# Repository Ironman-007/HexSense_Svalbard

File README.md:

# HexSense_Svalbard

The HexSense sensor node design for Svalbard mission in July, 2023

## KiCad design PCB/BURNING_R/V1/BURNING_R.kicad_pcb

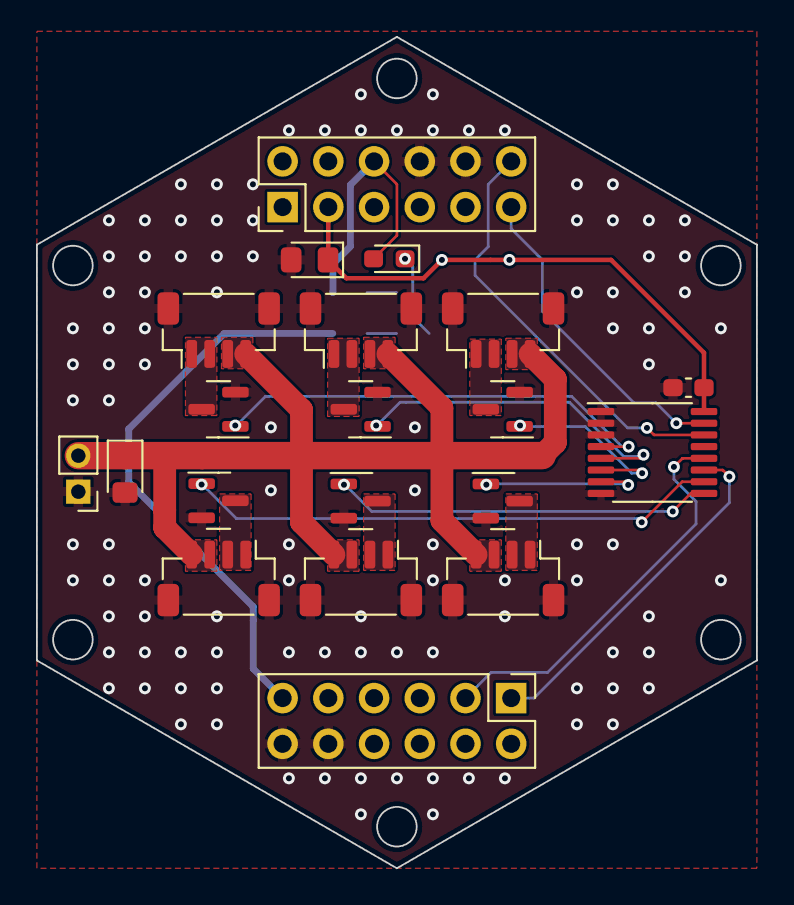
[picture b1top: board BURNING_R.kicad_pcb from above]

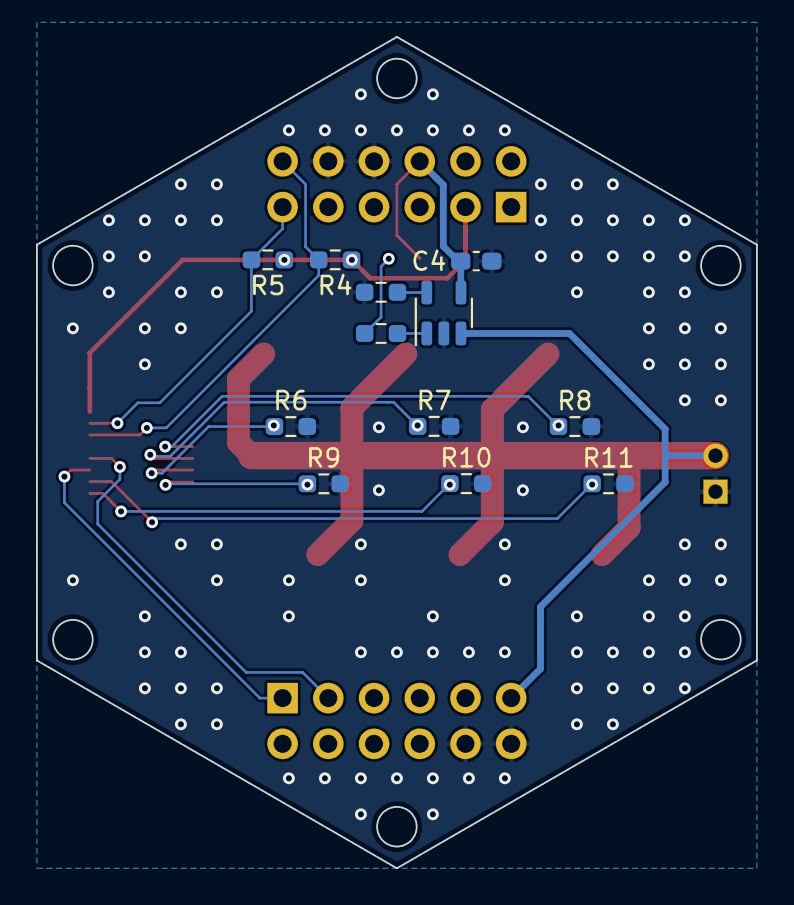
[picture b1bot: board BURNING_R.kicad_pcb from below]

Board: 2 copper layers, 40.0 x 46.2 mm, 32 parts (12 on the bottom side), 23 nets.

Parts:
C1, C3: 47uF; LED_0805_2012Metric_Pad1.15x1.40mm_HandSolder
C2, C4: 0.1uF; C_0603_1608Metric_Pad1.08x0.95mm_HandSolder
D1: RED; LED_0603_1608Metric_Pad1.05x0.95mm_HandSolder
J1, J2: Conn_02x06_Odd_Even; PinHeader_2x06_P2.54mm_Vertical
J3, J4, J5, J6, J7, J8: BR_conn; JST_SH_BM04B-SRSS-TB_1x04-1MP_P1.00mm_Vertical
J9: Battery; PinHeader_1x02_P2.00mm_Vertical
Q1, Q2, Q3, Q4, Q5, Q6: DMN2056U; SOT-23
R1, R2: 1k; R_0603_1608Metric_Pad0.98x0.95mm_HandSolder
R4, R5: NC; R_0603_1608Metric_Pad0.98x0.95mm_HandSolder
R6, R7, R8, R9, R10, R11: 10k; R_0603_1608Metric_Pad0.98x0.95mm_HandSolder
U1: TCA9534; TSSOP-16_4.4x5mm_P0.65mm
U2: MCP73831-2-OT; SOT-23-5

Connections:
+5V: C4.1, D1.2 (A), J1.6, U2.4 (VDD)
/BAT_BR: C3.1, J2.11, J3.3, J3.4, J4.3, J4.4, J5.3, J5.4, J6.3, J6.4, J7.3, J7.4, J8.3, J8.4, J9.2, U2.3 (VBAT)
/BR_1: J3.1, J3.2, Q1.3 (D)
/BR_1_EN: Q1.1 (G), R11.1, U1.10 (P5)
/BR_2: J4.1, J4.2, Q2.3 (D)
/BR_2_EN: Q2.1 (G), R10.1, U1.9 (P4)
/BR_3: J5.1, J5.2, Q3.3 (D)
/BR_3_EN: Q3.1 (G), R9.1, U1.7 (P3)
/BR_4: J6.1, J6.2, Q4.3 (D)
/BR_4_EN: Q4.1 (G), R8.1, U1.4 (P0)
/BR_5: J7.1, J7.2, Q5.3 (D)
/BR_5_EN: Q5.1 (G), R7.1, U1.5 (P1)
/BR_6: J8.1, J8.2, Q6.3 (D)
/BR_6_EN: Q6.1 (G), R6.1, U1.6 (P2)
/P1: J2.1, U1.11 (P6)
/P2: J2.3, U1.12 (P7)
/SCL: J1.12, R4.2, U1.14 (SCL)
/SDA: J1.11, R5.2, U1.15 (SDA)
GND: C1.2, C2.2, C3.2, C4.2, J1.8, J1.10, J2.10, J2.12, J3.MP, J4.MP, J5.MP, J6.MP, J7.MP, J8.MP, J9.1, Q1.2 (S), Q2.2 (S), Q3.2 (S), Q4.2 (S), Q5.2 (S), Q6.2 (S), R1.1, R6.2, R7.2, R8.2, R9.2, R10.2, R11.2, U1.1 (A0), U1.2 (A1), U1.3 (A2), U1.8 (GND), U2.2 (VSS)
unnamed: D1.1 (K), R2.2
unnamed: R1.2, U2.5 (PROG)
unnamed: R2.1, U2.1 (STAT)
VCC: C1.1, C2.1, J1.3, R4.1, R5.1, U1.16 (VDD)

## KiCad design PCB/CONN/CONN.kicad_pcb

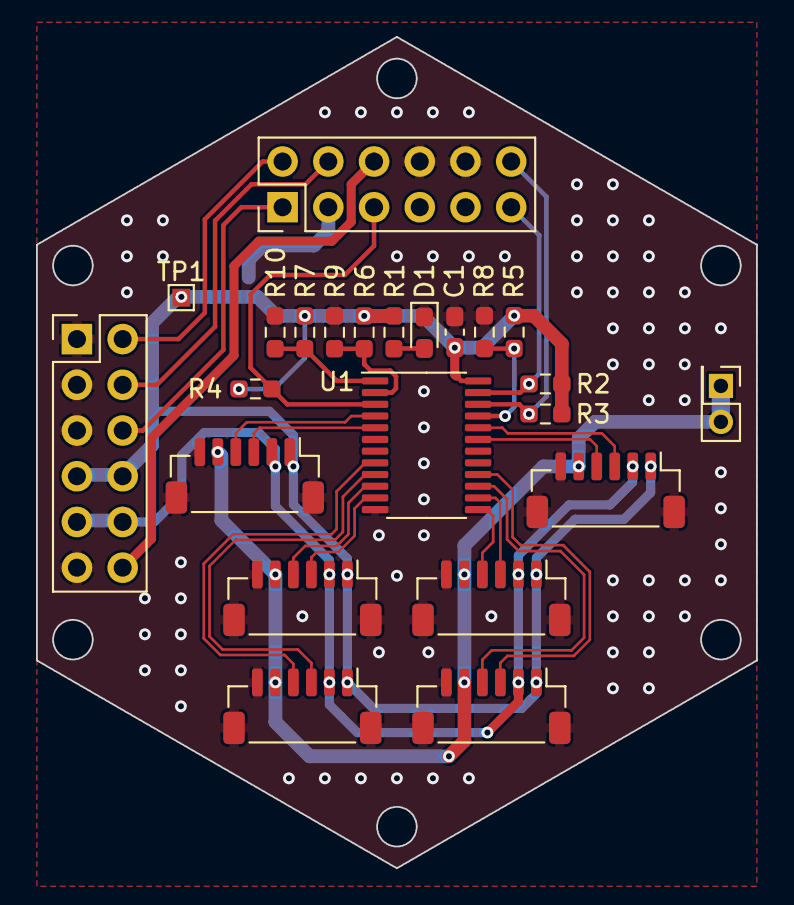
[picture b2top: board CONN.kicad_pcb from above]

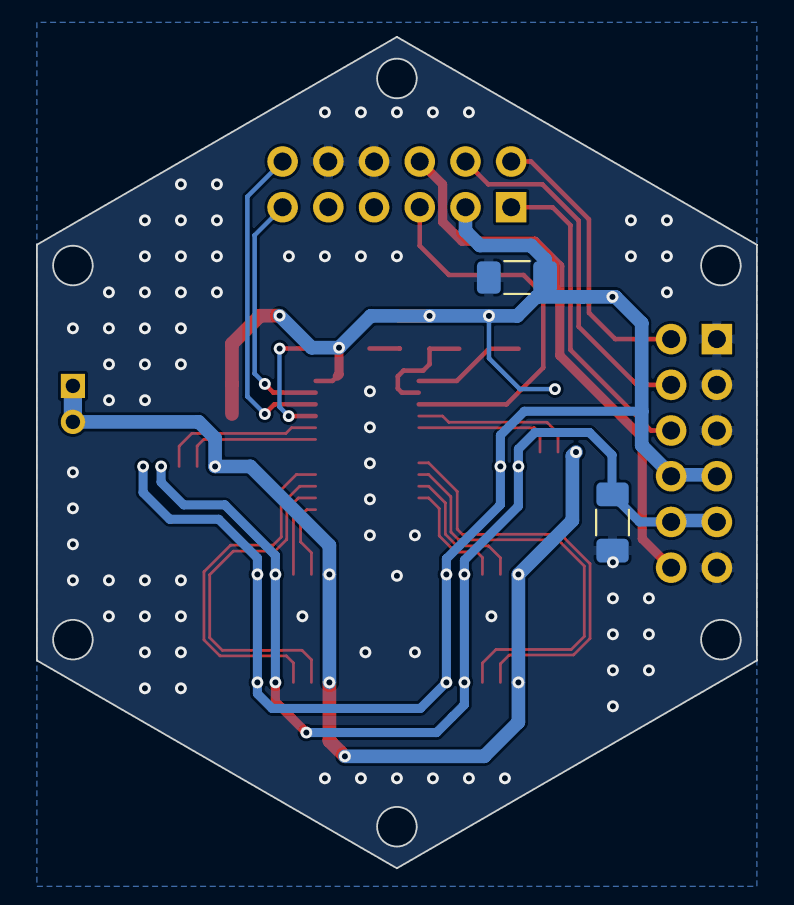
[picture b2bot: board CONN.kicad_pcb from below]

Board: 2 copper layers, 40.0 x 46.2 mm, 25 parts (2 on the bottom side), 27 nets.

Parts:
C1: 0.1uF; C_0603_1608Metric_Pad1.08x0.95mm_HandSolder
C2, C3: 47uF; C_1206_3216Metric_Pad1.33x1.80mm_HandSolder
D1: RED; LED_0603_1608Metric_Pad1.05x0.95mm_HandSolder
J1, J3: Conn_02x06_Odd_Even; PinHeader_2x06_P2.54mm_Vertical
J2: Solar cell; PinHeader_2x01_P2.00mm_Vertical
J4, J5, J6, J7, J8, J9: BM06B-SURS-TF(LF)(SN); JST_SH_BM06B-SRSS-TB_1x06-1MP_P1.00mm_Vertical
R1, R2, R3: 4.7K; R_0603_1608Metric_Pad0.98x0.95mm_HandSolder
R4, R8, R9, R10: 10k; R_0603_1608Metric_Pad0.98x0.95mm_HandSolder
R5, R6, R7: NC; R_0603_1608Metric_Pad0.98x0.95mm_HandSolder
TP1: TestPoint_Alt; TestPoint_Pad_1.0x1.0mm
U1: TCA9548APWR; TSSOP-24_4.4x7.8mm_P0.65mm

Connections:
+1V8: C3.1, J1.9, J1.10, J4.2, J5.2, J6.2, J7.2, J8.2, J9.2
+3V3: C1.1, C2.1, J1.7, J1.8, J3.3, J4.1, J5.1, J6.1, J7.1, J8.1, J9.1, R1.2, R2.2, R3.2, R4.2, R5.2, R6.2, R7.2, TP1.1, U1.24 (VCC)
+5V: J1.12, J3.6
/SC: J2.1, J2.2, J4.5, J5.5, J6.5, J7.5, J8.5, J9.5
/SCL: J3.12, R3.1, U1.22 (SCL)
/SCL0: J6.3, U1.5 (SC0)
/SCL2: J4.3, U1.9 (SC2)
/SCL3: J7.3, U1.11 (SC3)
/SCL4: J5.3, U1.14 (SC4)
/SCL5: J9.3, U1.16 (SC5)
/SCL7: J8.3, U1.20 (SC7)
/SDA: J3.11, R2.1, U1.23 (SDA)
/SDA0: J6.4, U1.4 (SD0)
/SDA2: J4.4, U1.8 (SD2)
/SDA3: J7.4, U1.10 (SD3)
/SDA4: J5.4, U1.13 (SD4)
/SDA5: J9.4, U1.15 (SD5)
/SDA7: J8.4, U1.19 (SD7)
/VBAT: J1.6, J3.1
/VBAT_OK: J1.4, J3.4
/~EN: J1.2, J3.2
/~RESET: J3.5, R4.1, U1.3 (~RESET)
GND: C1.2, C2.2, C3.2, D1.1 (K), J1.1, J1.3, J1.5, J1.11, J3.8, J3.10, J4.6, J4.MP, J5.6, J5.MP, J6.6, J6.MP, J7.6, J7.MP, J8.6, J8.MP, J9.6, J9.MP, R8.1, R9.1, R10.1, U1.12 (GND)
unnamed: D1.2 (A), R1.1
unnamed: R5.1, R8.2, U1.21 (A2)
unnamed: R6.1, R9.2, U1.2 (A1)
unnamed: R7.1, R10.2, U1.1 (A0)

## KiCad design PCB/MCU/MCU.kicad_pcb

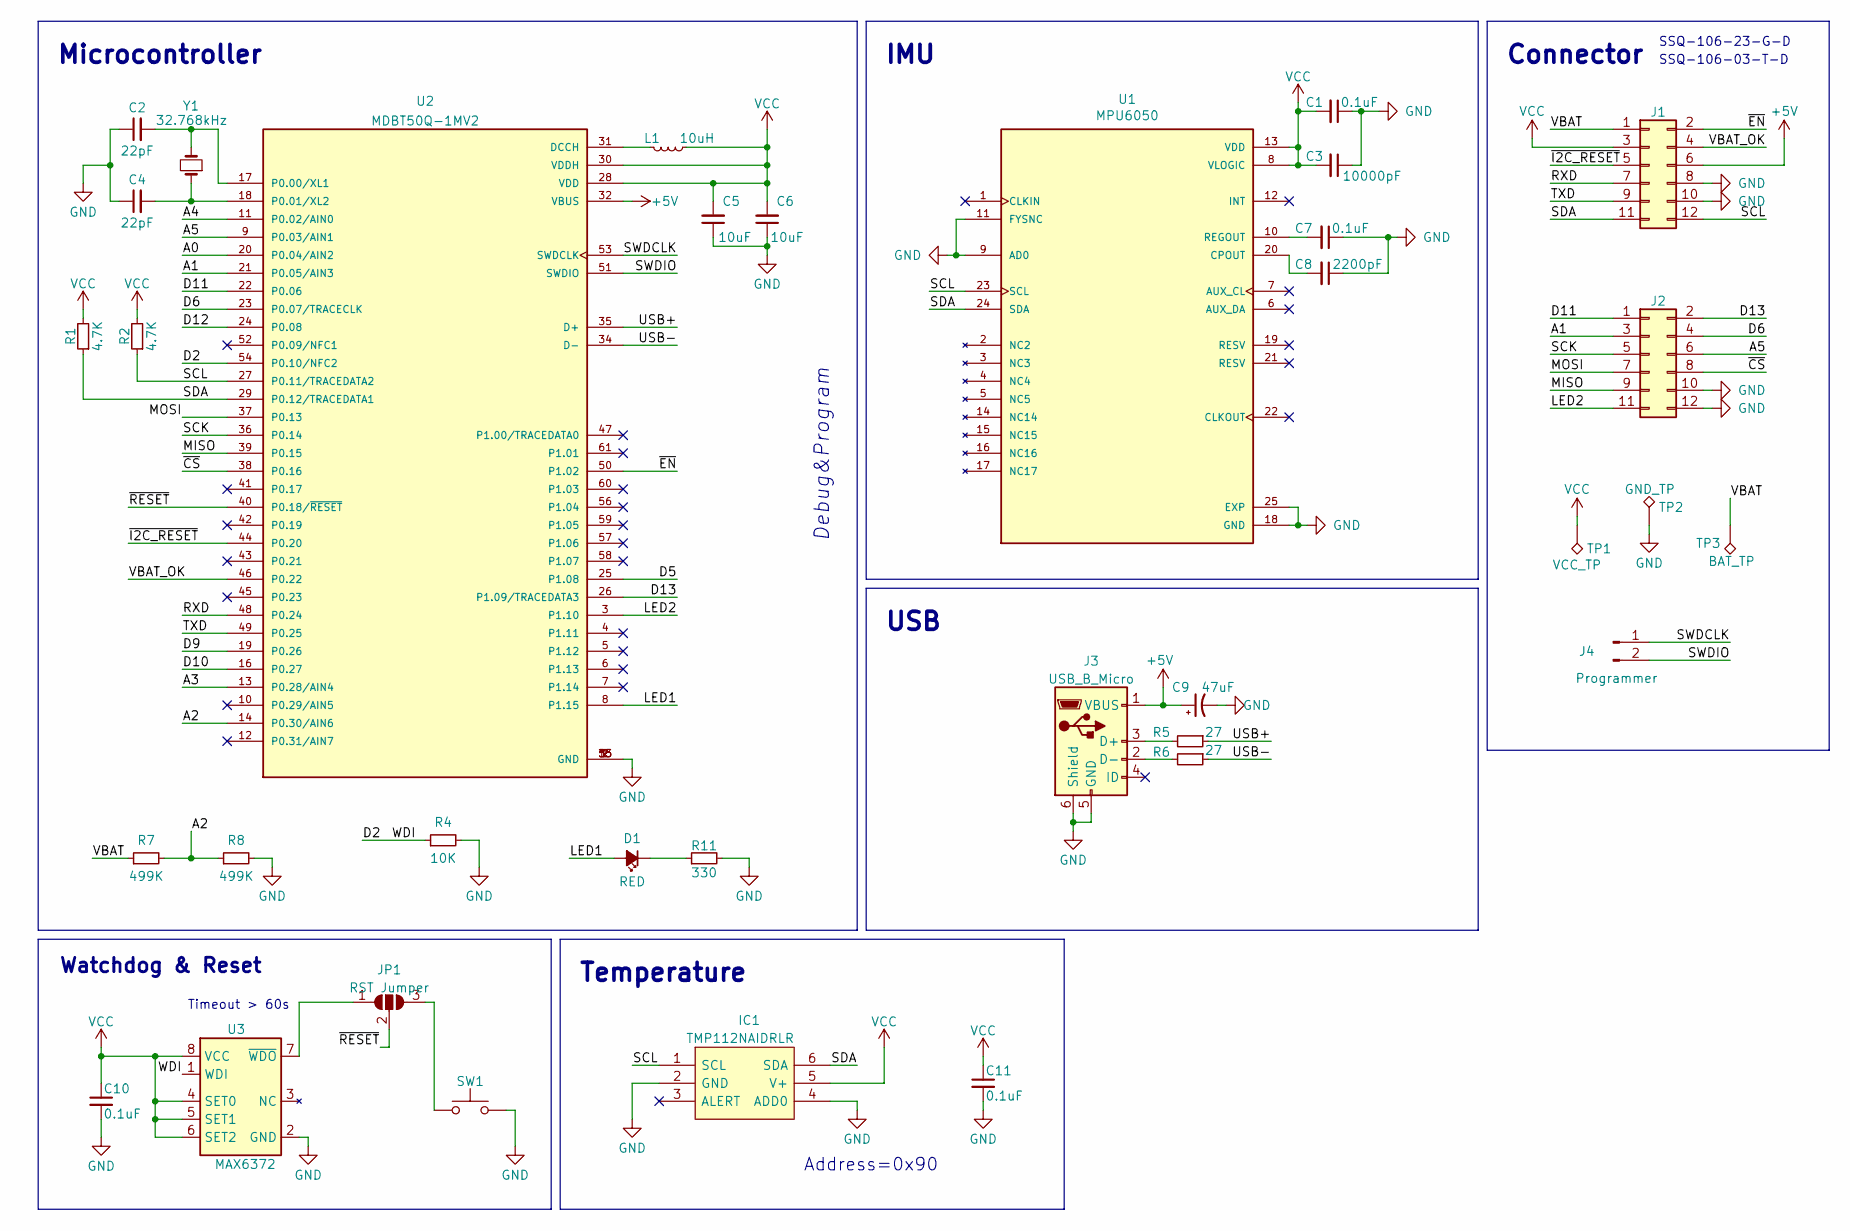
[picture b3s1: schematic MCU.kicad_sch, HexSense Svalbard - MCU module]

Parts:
C1, C7, C10, C11: 0.1uF; C_0402_1005Metric
C2, C4: 22pF; C_0402_1005Metric_Pad0.74x0.62mm_HandSolder
C3: 10000pF; C_0402_1005Metric
C5, C6: 10uF; C_0402_1005Metric_Pad0.74x0.62mm_HandSolder
C8: 2200pF; C_0402_1005Metric
C9: 47uF; C_0805_2012Metric_Pad1.18x1.45mm_HandSolder
D1: RED; LED_0603_1608Metric_Pad1.05x0.95mm_HandSolder
IC1: TMP112NAIDRLR; SOT50P160X60-6N; Manufacturer_Part_Number TMP112NAIDRLR; Mouser Part Number 595-TMP112NAIDRLR
J1, J2: Conn_02x06_Odd_Even; PinHeader_2x06_P2.54mm_Vertical
J3: USB_B_Micro; USB_Micro-B_Amphenol_10104110_Horizontal
J4: Programmer; PinHeader_1x02_P2.54mm_Vertical
JP1: RST Jumper; SolderJumper-3_P1.3mm_Open_RoundedPad1.0x1.5mm
L1: 10uH; L_0603_1608Metric_Pad1.05x0.95mm_HandSolder
R1, R2: 4.7K; R_0402_1005Metric_Pad0.72x0.64mm_HandSolder
R4: 10K; R_0402_1005Metric
R5, R6: 27; R_0402_1005Metric_Pad0.72x0.64mm_HandSolder
R7, R8: 499K; R_0402_1005Metric_Pad0.72x0.64mm_HandSolder
R11: 330; R_0402_1005Metric_Pad0.72x0.64mm_HandSolder
SW1: SW_Push; SW_Push_1P1T_NO_CK_KMR2
TP1: VCC_TP; TestPoint_Pad_1.5x1.5mm
TP2: GND_TP; TestPoint_Pad_1.5x1.5mm
TP3: BAT_TP; TestPoint_Pad_1.0x1.0mm
U1: MPU6050; IC_MPU6050; PARTREV 3.4
U2: MDBT50Q-1MV2; XCVR_MDBT50Q-1MV2; PARTREV H
U3: MAX6372; SOT-23-8
Y1: 32.768kHz; C_0805_2012Metric_Pad1.18x1.45mm_HandSolder

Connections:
+5V: C9.1, J1.6, J3.1 (VBUS), U2.32 (VBUS)
/A0: U2.20 (P0.04/AIN2)
/A1: J2.3, U2.21 (P0.05/AIN3)
/A2: R7.2, R8.1, U2.14 (P0.30/AIN6)
/A3: U2.13 (P0.28/AIN4)
/A4: U2.11 (P0.02/AIN0)
/A5: J2.6, U2.9 (P0.03/AIN1)
/D2: R4.1, U2.54 (P0.10/NFC2), U3.1 (WDI)
/D5: U2.25 (P1.08)
/D6: J2.4, U2.23 (P0.07/TRACECLK)
/D9: U2.19 (P0.26)
/D10: U2.16 (P0.27)
/D11: J2.1, U2.22 (P0.06)
/D12: U2.24 (P0.08)
/D13: J2.2, U2.26 (P1.09/TRACEDATA3)
/LED1: D1.2 (A), U2.8 (P1.15)
/LED2: J2.11, U2.3 (P1.10)
/MISO: J2.9, U2.39 (P0.15)
/MOSI: J2.7, U2.37 (P0.13)
/RXD: J1.7, U2.48 (P0.24)
/SCK: J2.5, U2.36 (P0.14)
/SCL: IC1.1 (SCL), J1.12, R2.1, U1.23 (SCL), U2.27 (P0.11/TRACEDATA2)
/SDA: IC1.6 (SDA), J1.11, R1.1, U1.24 (SDA), U2.29 (P0.12/TRACEDATA1)
/SWDCLK: J4.1, U2.53 (SWDCLK)
/SWDIO: J4.2, U2.51 (SWDIO)
/TXD: J1.9, U2.49 (P0.25)
/USB+: R5.1, U2.35 (D+)
/USB-: R6.1, U2.34 (D-)
/VBAT: J1.1, R7.1, TP3.1
/VBAT_OK: J1.4, U2.46 (P0.22)
/~CS: J2.8, U2.38 (P0.16)
/~EN: J1.2, U2.50 (P1.02)
/~I2C_RESET: J1.5, U2.44 (P0.20)
/~RESET: JP1.2 (C), U2.40 (P0.18/~RESET)
GND: C1.1, C2.1, C3.1, C4.1, C5.1, C6.1, C7.1, C8.1, C9.2, C10.2, C11.2, IC1.2 (GND), IC1.4 (ADD0), J1.8, J1.10, J2.10, J2.12, J3.5 (GND), J3.6 (Shield), R4.2, R8.2, R11.2, SW1.2, TP2.1, U1.9 (AD0), U1.11 (FYSNC), U1.18 (GND), U1.25 (EXP), U2.1 (GND), U2.2 (GND), U2.15 (GND), U2.33 (GND), U2.55 (GND), U3.2 (GND)
unnamed: D1.1 (K), R11.1
unnamed: J3.3 (D+), R5.2
unnamed: J3.2 (D-), R6.2
unnamed: JP1.1 (A), U3.7 (~WDO)
unnamed: JP1.3 (B), SW1.1
unnamed: C8.2, U1.20 (CPOUT)
unnamed: C7.2, U1.10 (REGOUT)
unnamed: L1.2, U2.31 (DCCH)
unnamed: C2.2, U2.17 (P0.00/XL1), Y1.2
unnamed: C4.2, U2.18 (P0.01/XL2), Y1.1
VCC: C1.2, C3.2, C5.2, C6.2, C10.1, C11.1, IC1.5 (V+), J1.3, L1.1, R1.2, R2.2, TP1.1, U1.8 (VLOGIC), U1.13 (VDD), U2.28 (VDD), U2.30 (VDDH), U3.4 (SET0), U3.5 (SET1), U3.6 (SET2), U3.8 (VCC)

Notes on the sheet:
Debug&Program
IMU
SSQ-106-03-T-D
Microcontroller
Temperature
Timeout > 60s
Watchdog & Reset
USB
Connector
Address=0x90
SSQ-106-23-G-D

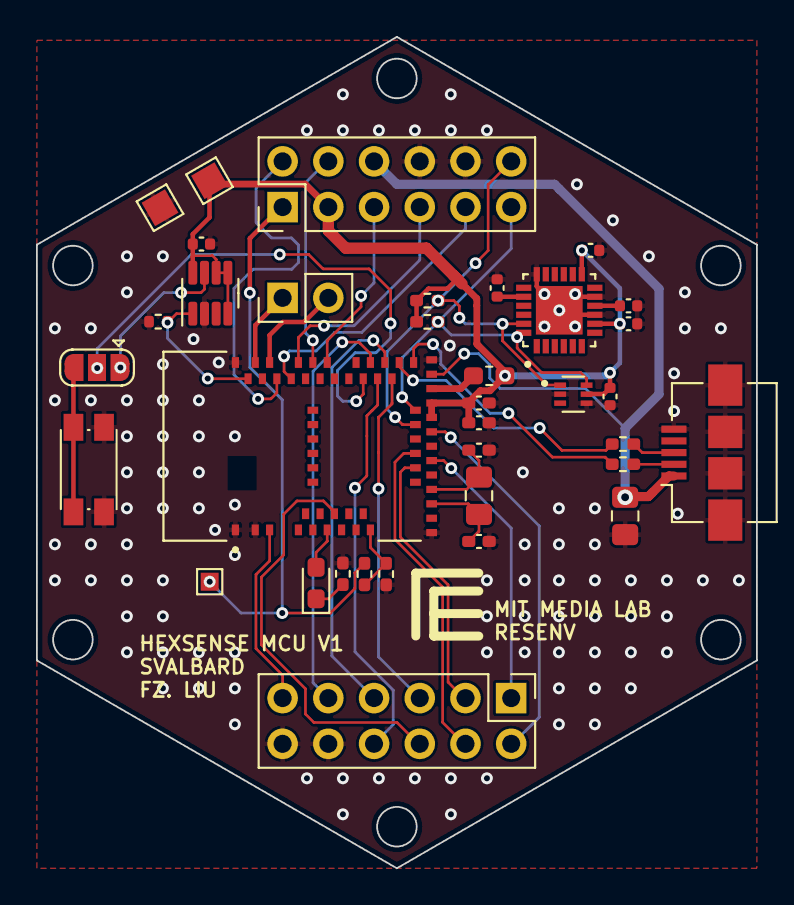
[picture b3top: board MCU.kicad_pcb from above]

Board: 2 copper layers, 40.0 x 46.2 mm, 35 parts (0 on the bottom side), 39 nets.

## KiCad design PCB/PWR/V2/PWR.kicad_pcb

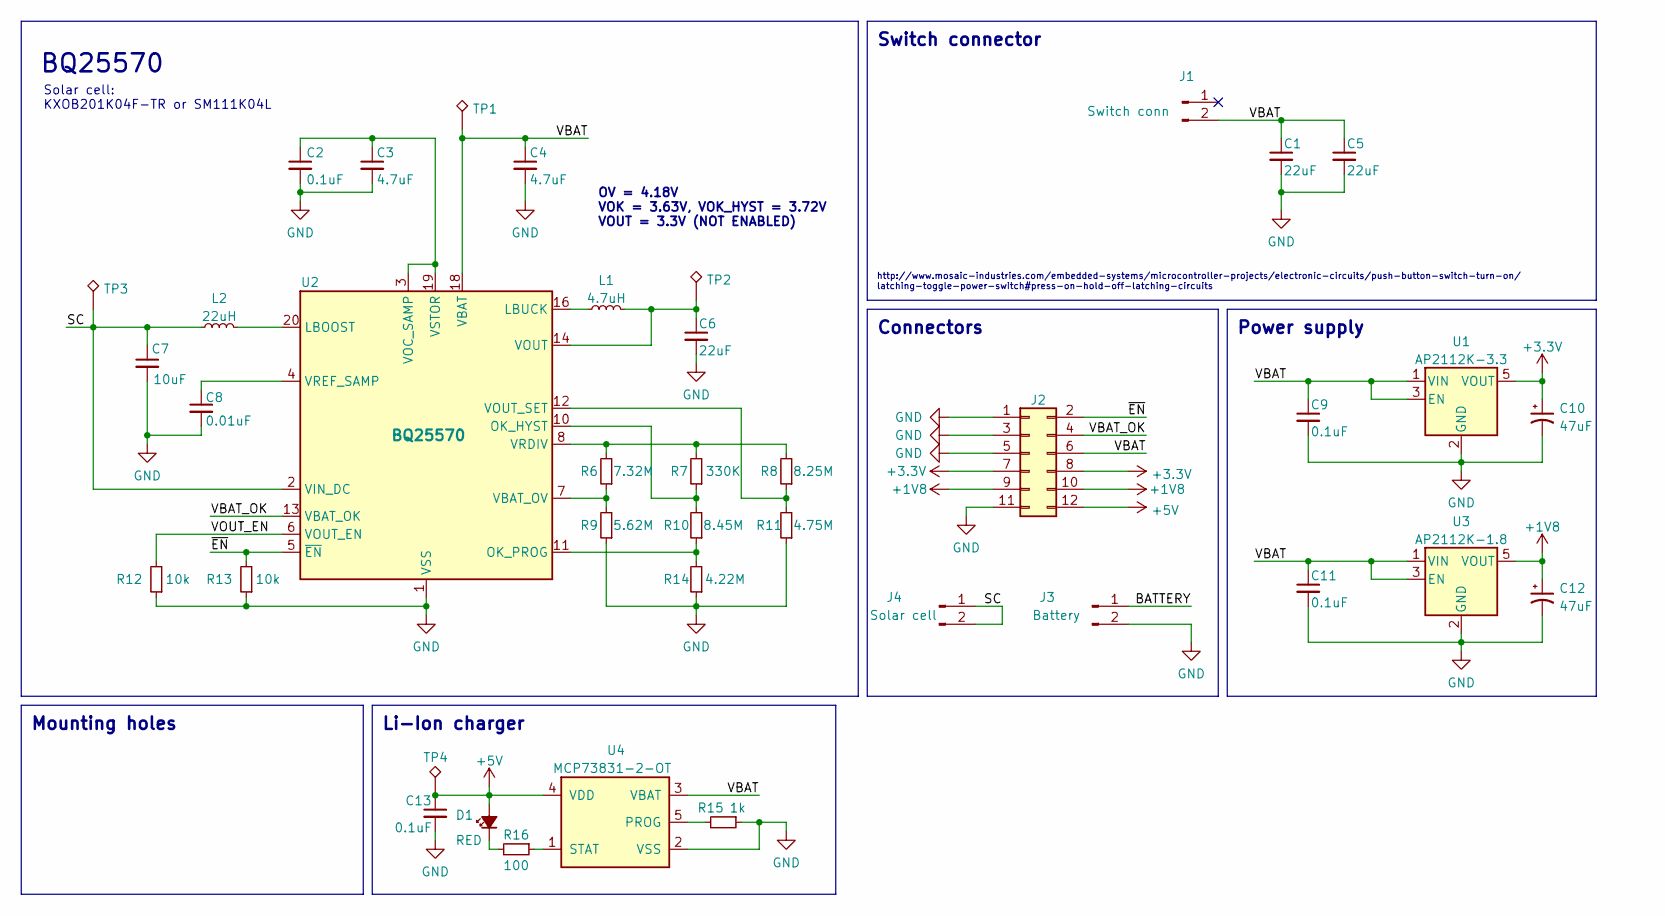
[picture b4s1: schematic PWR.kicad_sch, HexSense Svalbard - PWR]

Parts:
C1, C5: 22uF; C_1206_3216Metric_Pad1.33x1.80mm_HandSolder
C2, C9, C11, C13: 0.1uF; C_0402_1005Metric_Pad0.74x0.62mm_HandSolder
C3, C4: 4.7uF; C_0603_1608Metric_Pad1.08x0.95mm_HandSolder
C6: 22uF; C_0805_2012Metric_Pad1.18x1.45mm_HandSolder
C7: 10uF; C_0603_1608Metric_Pad1.08x0.95mm_HandSolder
C8: 0.01uF; C_0402_1005Metric_Pad0.74x0.62mm_HandSolder
C10, C12: 47uF; LED_0805_2012Metric_Pad1.15x1.40mm_HandSolder
D1: RED; LED_0603_1608Metric_Pad1.05x0.95mm_HandSolder
J1: Switch conn; PinHeader_1x02_P2.54mm_Vertical
J2: Conn_02x06_Odd_Even; PinHeader_2x06_P2.54mm_Vertical
J3: Battery; PinHeader_2x01_P2.00mm_Vertical
J4: Solar cell; PinHeader_2x01_P2.00mm_Vertical
L1: 4.7uH; L_Wuerth_MAPI-3015
L2: 22uH; L_Taiyo-Yuden_NR-40xx_HandSoldering
R6: 7.32M; R_0603_1608Metric_Pad0.98x0.95mm_HandSolder
R7: 330K; R_0603_1608Metric_Pad0.98x0.95mm_HandSolder
R8: 8.25M; R_0603_1608Metric_Pad0.98x0.95mm_HandSolder
R9: 5.62M; R_0603_1608Metric_Pad0.98x0.95mm_HandSolder
R10: 8.45M; R_0603_1608Metric_Pad0.98x0.95mm_HandSolder
R11: 4.75M; R_0603_1608Metric_Pad0.98x0.95mm_HandSolder
R12, R13: 10k; R_0603_1608Metric_Pad0.98x0.95mm_HandSolder
R14: 4.22M; R_0603_1608Metric_Pad0.98x0.95mm_HandSolder
R15: 1k; R_0603_1608Metric_Pad0.98x0.95mm_HandSolder
R16: 100; R_0603_1608Metric_Pad0.98x0.95mm_HandSolder
TP1, TP2, TP3, TP4: TestPoint_Alt; TestPoint_Pad_1.0x1.0mm
U1: AP2112K-3.3; SOT-23-5
U2: BQ25570; QFN-20-1EP_3.5x3.5mm_P0.5mm_EP2x2mm
U3: AP2112K-1.8; SOT-23-5
U4: MCP73831-2-OT; SOT-23-5

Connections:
+1V8: C12.1, J2.9, J2.10, U3.5 (VOUT)
+3V3: C10.1, J2.7, J2.8, U1.5 (VOUT)
+5V: C13.1, D1.2 (A), J2.12, TP4.1, U4.4 (VDD)
/BATTERY: J3.1
/SC: C7.1, J4.1, J4.2, L2.1, TP3.1, U2.2 (VIN_DC)
/VBAT: C1.1, C4.1, C5.1, C9.1, C11.1, J1.2, J2.6, TP1.1, U1.1 (VIN), U1.3 (EN), U2.18 (VBAT), U3.1 (VIN), U3.3 (EN), U4.3 (VBAT)
/VBAT_OK: J2.4, U2.13 (VBAT_OK)
/VOUT_EN: R12.2, U2.6 (VOUT_EN)
/~EN: J2.2, R13.2, U2.5 (~EN)
GND: C1.2, C2.2, C3.2, C4.2, C5.2, C6.2, C7.2, C8.2, C9.2, C10.2, C11.2, C12.2, C13.2, J2.1, J2.3, J2.5, J2.11, J3.2, R9.1, R11.1, R12.1, R13.1, R14.1, R15.1, U1.2 (GND), U2.1 (VSS), U2.9 (VSS), U2.15 (VSS), U2.17 (VSS), U2.21 (VSS), U3.2 (GND), U4.2 (VSS)
unnamed: D1.1 (K), R16.2
unnamed: L2.2, U2.20 (LBOOST)
unnamed: L1.1, U2.16 (LBUCK)
unnamed: R7.1, R10.2, U2.10 (OK_HYST)
unnamed: R10.1, R14.2, U2.11 (OK_PROG)
unnamed: R6.1, R9.2, U2.7 (VBAT_OV)
unnamed: C2.1, C3.1, U2.3 (VOC_SAMP), U2.19 (VSTOR)
unnamed: C6.1, L1.2, TP2.1, U2.14 (VOUT)
unnamed: R8.1, R11.2, U2.12 (VOUT_SET)
unnamed: R6.2, R7.2, R8.2, U2.8 (VRDIV)
unnamed: C8.1, U2.4 (VREF_SAMP)
unnamed: R15.2, U4.5 (PROG)
unnamed: R16.1, U4.1 (STAT)

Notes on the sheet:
Li-Ion charger
BQ25570
Switch connector
Mounting holes
Solar cell: KXOB201K04F-TR or SM111K04L
OV = 4.18V VOK = 3.63V, VOK_HYST = 3.72V VOUT = 3.3V (NOT ENABLED)
Power supply
http://www.mosaic-industries.com/embedded-systems/microcontroller-projects/electronic-circuits/push-button-switch-turn-on/ latching-toggle-power-switch#press-on-hold-off-latching-circuits
Connectors

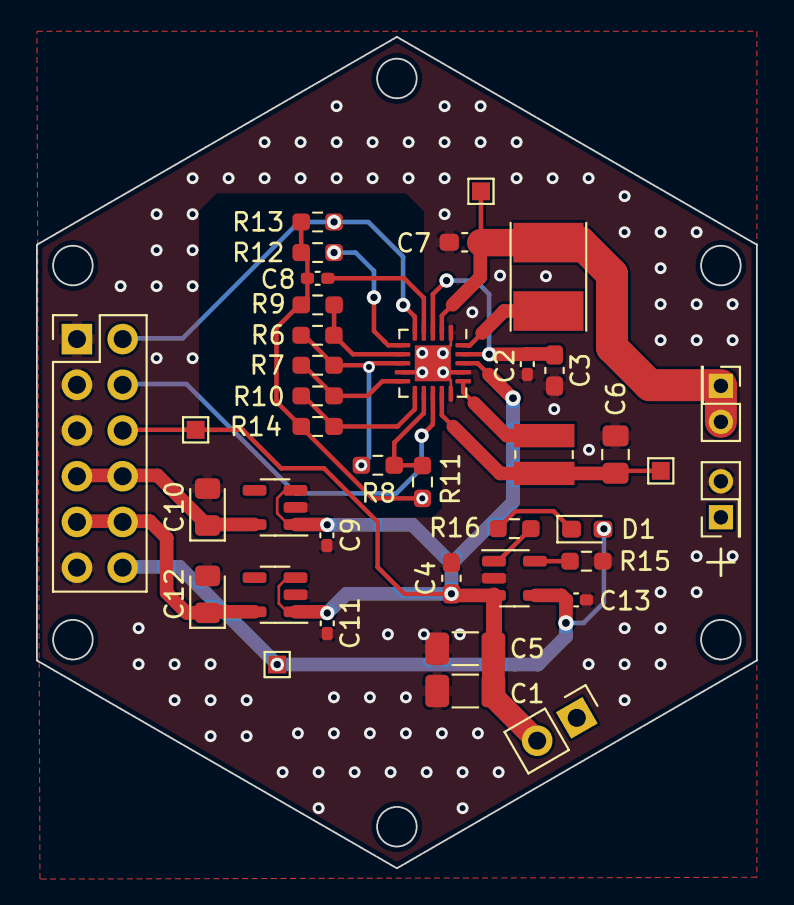
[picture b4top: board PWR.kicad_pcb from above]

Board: 2 copper layers, 40.0 x 46.2 mm, 39 parts (0 on the bottom side), 22 nets.

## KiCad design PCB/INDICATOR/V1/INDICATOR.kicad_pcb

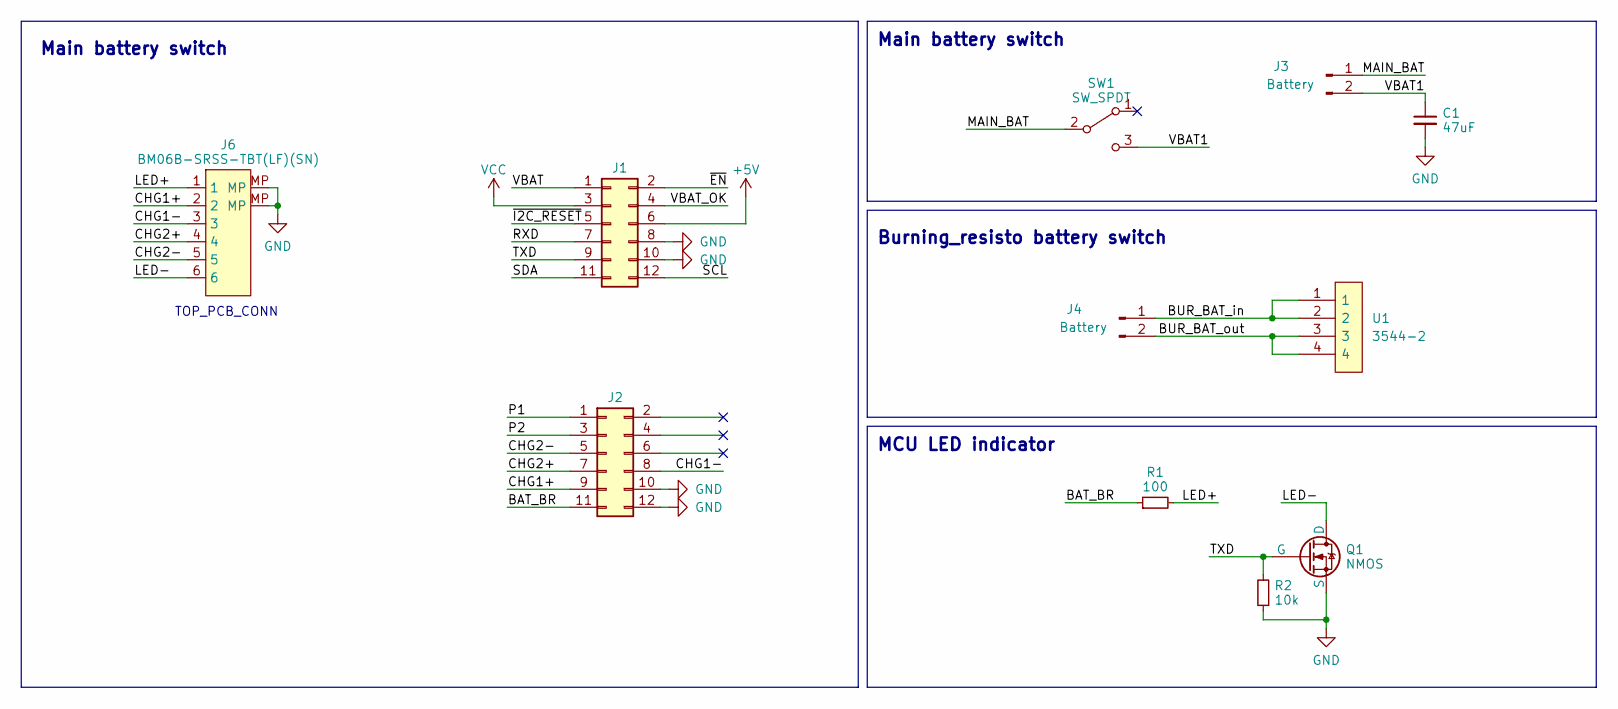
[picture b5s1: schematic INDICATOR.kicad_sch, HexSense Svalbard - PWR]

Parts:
C1: 47uF; CP_EIA-6032-15_Kemet-U_Pad2.25x2.35mm_HandSolder
J1, J2: Conn_02x06_Odd_Even; PinHeader_2x06_P2.54mm_Vertical
J3, J4: Battery; PinHeader_2x01_P2.00mm_Vertical
J6: BM06B-SRSS-TBT(LF)(SN); JST_SH_BM06B-SRSS-TB_1x06-1MP_P1.00mm_Vertical
Q1: NMOS; SOT-23
R1: 100; R_0603_1608Metric_Pad0.98x0.95mm_HandSolder
R2: 10k; R_0603_1608Metric_Pad0.98x0.95mm_HandSolder
SW1: SW_SPDT; PinHeader_1x03_P2.54mm_Vertical
U1: 3544-2; Manufacturer_Part_Number 3544-2; Mouser Part Number 534-3544-2

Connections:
+5V: J1.6
/BAT_BR: J2.11, R1.1
/BUR_BAT_in: J4.1, U1.1, U1.2
/BUR_BAT_out: J4.2, U1.3, U1.4
/CHG1+: J2.9, J6.2
/CHG1-: J2.8, J6.3
/CHG2+: J2.7, J6.4
/CHG2-: J2.5, J6.5
/LED+: J6.1, R1.2
/LED-: J6.6, Q1.1 (D)
/MAIN_BAT: J3.1, SW1.2 (B)
/P1: J2.1
/P2: J2.3
/RXD: J1.7
/SCL: J1.12
/SDA: J1.11
/TXD: J1.9, Q1.2 (G), R2.2
/VBAT: J1.1
/VBAT1: C1.1, J3.2, SW1.3 (C)
/VBAT_OK: J1.4
/~EN: J1.2
/~I2C_RESET: J1.5
GND: C1.2, J1.8, J1.10, J2.10, J2.12, J6.MP, Q1.3 (S), R2.1
VCC: J1.3

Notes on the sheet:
Main battery switch
Burning_resisto battery switch
MCU LED indicator
TOP_PCB_CONN

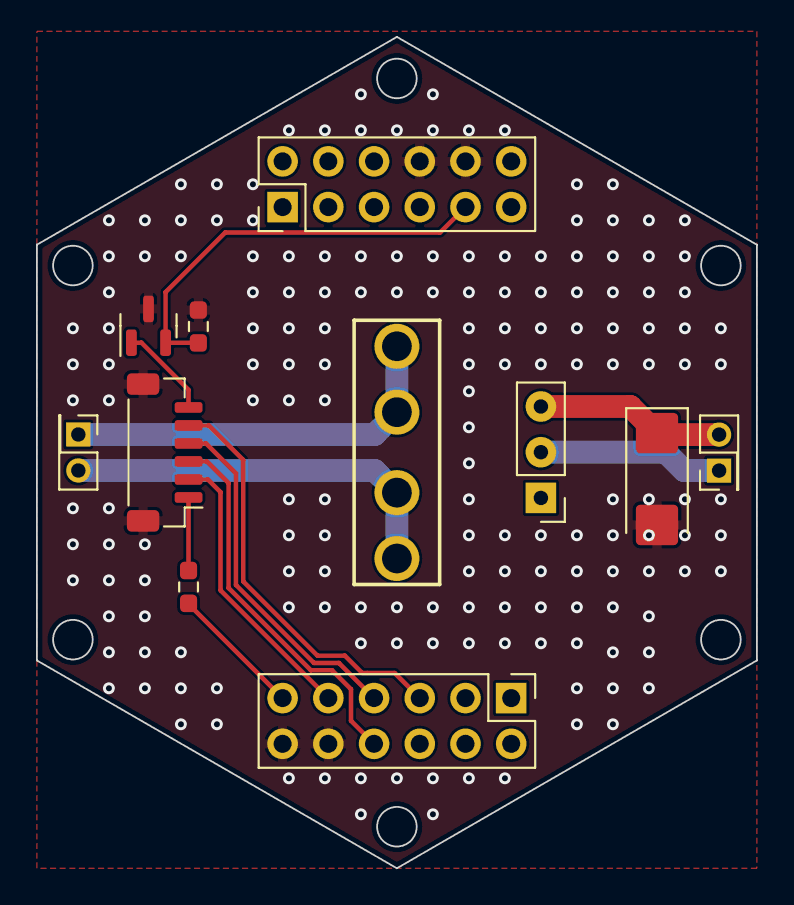
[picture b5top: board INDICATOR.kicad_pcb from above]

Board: 2 copper layers, 40.0 x 46.2 mm, 11 parts (0 on the bottom side), 13 nets.

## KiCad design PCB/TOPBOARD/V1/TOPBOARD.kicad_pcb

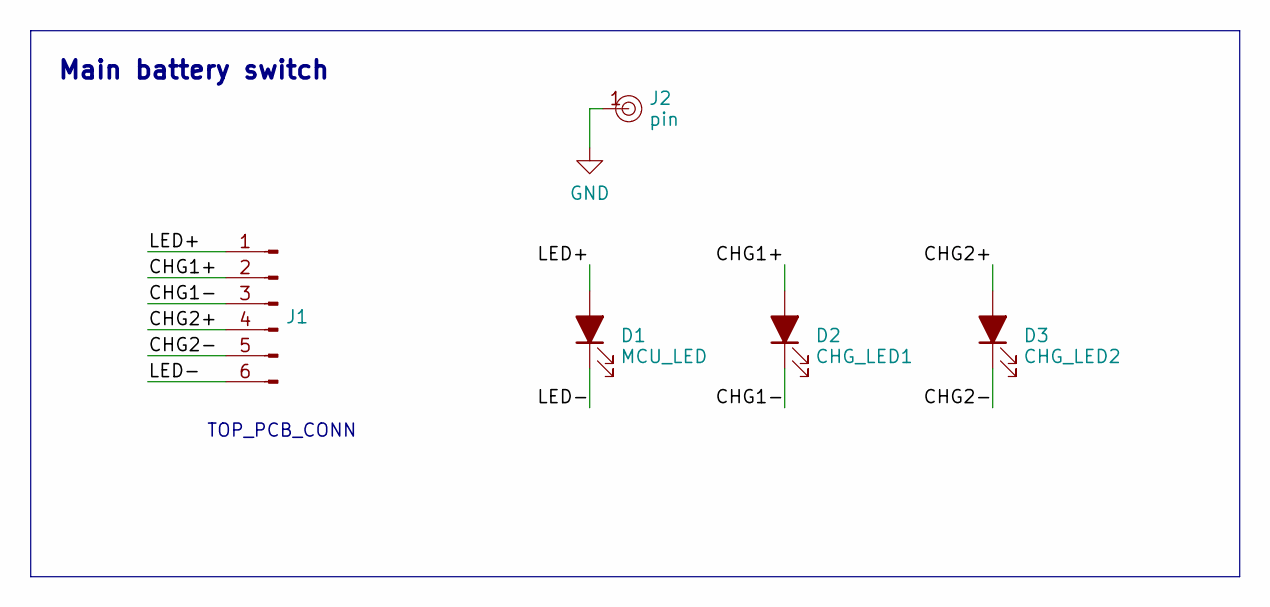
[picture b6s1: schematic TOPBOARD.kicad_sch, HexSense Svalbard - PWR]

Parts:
D1: MCU_LED; LED_0603_1608Metric_Pad1.05x0.95mm_HandSolder
D2: CHG_LED1; LED_0603_1608Metric_Pad1.05x0.95mm_HandSolder
D3: CHG_LED2; LED_0603_1608Metric_Pad1.05x0.95mm_HandSolder
J1: Conn_01x06_Pin; FZ_SMD_01x06_2.00mm
J2: pin; 1_pin_SMD_1.5mmx1.0mm

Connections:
/CHG1+: D2.2 (A), J1.2
/CHG1-: D2.1 (K), J1.3
/CHG2+: D3.2 (A), J1.4
/CHG2-: D3.1 (K), J1.5
/LED+: D1.2 (A), J1.1
/LED-: D1.1 (K), J1.6
GND: J2.1

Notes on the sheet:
Main battery switch
TOP_PCB_CONN

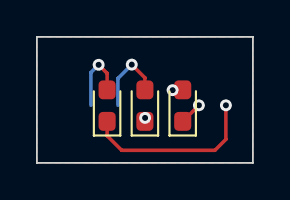
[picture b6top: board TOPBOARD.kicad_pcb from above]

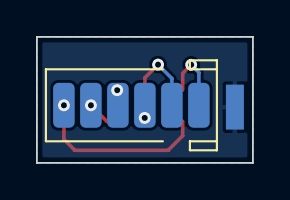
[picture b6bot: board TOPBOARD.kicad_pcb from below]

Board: 2 copper layers, 12.0 x 7.0 mm, 5 parts (2 on the bottom side), 6 nets.

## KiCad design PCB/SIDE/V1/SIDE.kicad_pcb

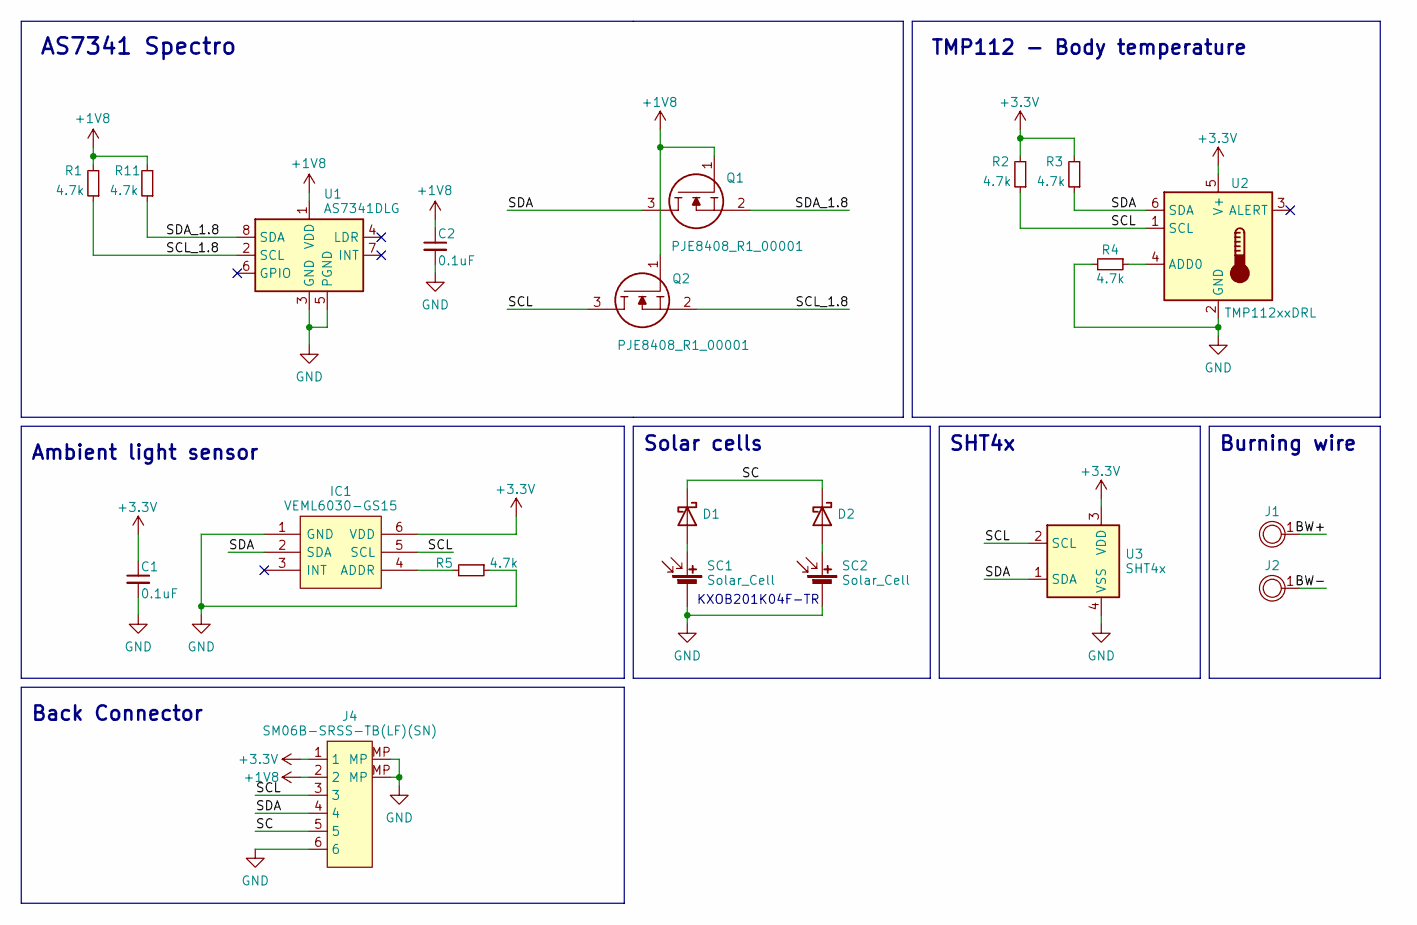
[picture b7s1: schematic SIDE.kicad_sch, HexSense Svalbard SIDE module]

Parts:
C1, C2: 0.1uF; C_0603_1608Metric_Pad1.08x0.95mm_HandSolder
D1, D2: D_Schottky; D_0805_2012Metric_Pad1.15x1.40mm_HandSolder
IC1: VEML6030-GS15; VEML6030GS15; Manufacturer_Part_Number VEML6030-GS15; Mouser Part Number 78-VEML6030-GS15
J1, J2: 1_PIN; 1_pin_SMD_1.5mmx1.0mm
J4: SM06B-SRSS-TB(LF)(SN); JST_SH_SM06B-SRSS-TB_1x06-1MP_P1.00mm_Horizontal
Q1, Q2: PJE8408_R1_00001; SOTFL50P160X60-3N; Manufacturer_Part_Number PJE8408_R1_00001; Mouser Part Number 241-PJE8408_R1_00001
R1, R2, R3, R4, R5, R11: 4.7k; R_0603_1608Metric_Pad0.98x0.95mm_HandSolder
SC1, SC2: Solar_Cell; KXOB201K04F-TR
U1: AS7341DLG; AMS_OLGA-8_2x3.1mm_P0.8mm
U2: TMP112xxDRL; SOT-563
U3: SHT4x; Sensirion_DFN-4_1.5x1.5mm_P0.8mm_SHT4x_NoCentralPad

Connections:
+1V8: C2.1, J4.2, Q1.1, Q2.1, R1.2, R11.2, U1.1 (VDD)
+3V3: C1.1, IC1.6 (VDD), J4.1, R2.2, R3.2, U2.5 (V+), U3.3 (VDD)
/BW+: J1.1
/BW-: J2.1
/SC: D1.1 (K), D2.1 (K), J4.5
/SCL: IC1.5 (SCL), J4.3, Q2.3, R2.1, U2.1 (SCL), U3.2 (SCL)
/SCL_1.8: Q2.2, R1.1, U1.2 (SCL)
/SDA: IC1.2 (SDA), J4.4, Q1.3, R3.1, U2.6 (SDA), U3.1 (SDA)
/SDA_1.8: Q1.2, R11.1, U1.8 (SDA)
GND: C1.2, C2.2, IC1.1 (GND), J4.6, J4.MP, R4.2, R5.1, SC1.2 (-), SC2.2 (-), U1.3 (GND), U1.5 (PGND), U2.2 (GND), U3.4 (VSS)
unnamed: D1.2 (A), SC1.1 (+)
unnamed: D2.2 (A), SC2.1 (+)
unnamed: IC1.4 (ADDR), R5.2
unnamed: R4.1, U2.4 (ADD0)

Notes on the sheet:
Burning wire
Back Connector
TMP112 - Body temperature
KXOB201K04F-TR
Solar cells
SHT4x
AS7341 Spectro
Ambient light sensor

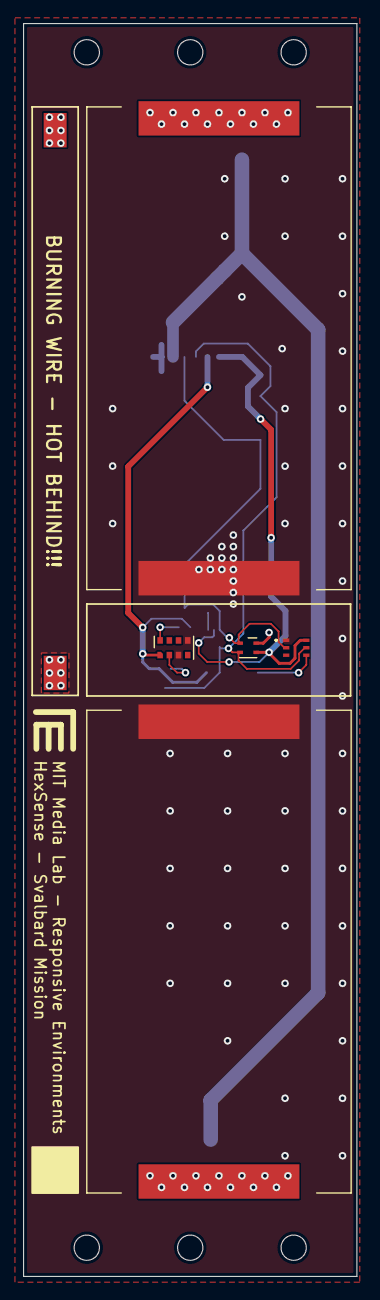
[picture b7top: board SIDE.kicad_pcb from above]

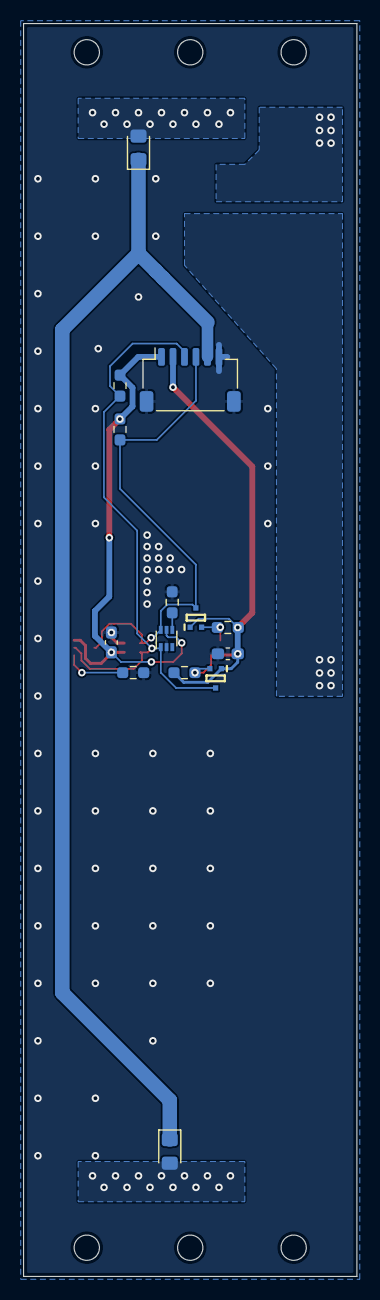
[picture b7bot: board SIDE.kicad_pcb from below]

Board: 2 copper layers, 29.0 x 109.0 mm, 21 parts (14 on the bottom side), 12 nets.
